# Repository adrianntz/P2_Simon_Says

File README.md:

# P2_Simon_Says
Proiect Simplu proiectat cu microcontroller AVR ATMEGA164A pentru a creea un joc simplu de tip Simon Says, folosind 4 butoane pentru user input si 4 led-uri pentru system output. 

## Inspiratie Proiect
Ideea de functionare a jocului a fost preluata din acest proiect pe arduino:

https://youtu.be/xLLTxN_UBnI

## Firmware Architecture
Bootloader-ul pentru Atmega164A este deja incarcat inainte de primirea chip-ului. Firmware-ul poate fi flashed folosind programul AvrBuster.exe
Firmware-ul pentru Atmega164A este scris in C folosind compilatorul CodeVisionAVR ANSI C Compiler si IDE-ul CodeVisionAVR. Codul in C  a fost creat folosind Code Wizard-ul IDE-ului.
Pentru jocul Simon Says vom folosi doar Portul B al microcontrollerului. Astfel, cu Code Wizard am initializat Pinii PB0->3 ca input si conectati la rezistorul pull-up intern, acesti pini fiind conectati la switch-uri, iar pinii PB4->7 sunt de tip output prin care aprindem LED-urile.
Codul are ca structura principala doi vectori de lungime MAX_LEVEL, unul fiind lista de secvente a nivelului si al doilea fiind secventa introdusa de catre jucator.
Astfel, lungimea jocului poate fi setata folosind MAX_LEVEL. La pornirea firmware-ului se umple vectorul nivelului cu valori randomizate intre 0 si 4. De-a lungul jocului se completeaza si vectorul cu secventele introduse de jucator, si se vor compara ce doi vetori. In momentul in care se greseste o secventa sau se ajunge la lungimea maxima, se termina jocul si se reseteaza vectorii.
De asemenea Firmware-ul are implementat o dificultate a jocului, anume viteza afisarii secventei curente. Cu cat este mai avansat jocul intr-o secventa mai mare, aceasta viteza creste, facand jocul mai dificil cu cat te joci mai mult.

Utilizare Memorie Firmware:
EEPROM usage: 0 byte(s), 0.0% of EEPROM

Program size: 646 words (1292 bytes), 7.9% of FLASH

RAM Global variables size: 404 byte(s)

Estimated Data Stack usage: 6 byte(s)

(Informatie data de compilator)

## Hadware Description
Placuta THT este compusa dintr-un microcontroller ATMEGA164A cu footprint THD si componentele sale auxiliare (condensatoare, quartz si un LED pentru verificare), iar portul A al microcontrollerului este impartit jumate in input si output. Jumatea de input a portului B este conectat la 4 butoane la GND, iar jumatea de output este conectat la 4 led-uri. Alimentarea se face printr-un USB bridge bazat pe chip-ul CH340G USB to Serial Converter.

Varianta SMD introduce un package mai mic pentru toate componentele, ATMEGA164A fiind pe footprint TQFP si toate rezistoarele, condensatoare si led-urile pe footprint 0805. Bridge-ul USB to Serial este incorporat in placuta conectat la un port micro-USB pus pe placuta.
## Hardware Schematic 

## Hardware PCB Layout

## BOM 

| Component Count:               | 39   |                   |                                                            |                                                         |
|--------------------------------|------|-------------------|------------------------------------------------------------|---------------------------------------------------------|
| Ref                            | Qnty | Value             | Footprint                                                  | Description                                             |
| C1, C5,                        | 2    | 18p               | Capacitor_SMD:C_0805_2012Metric                            | Capacitor symbol for simulation only                    |
| C2, C4, C6, C11,               | 4    | 100n              | Capacitor_SMD:C_0805_2012Metric                            | Capacitor symbol for simulation only                    |
| C3,                            | 1    | 1u                | Capacitor_Tantalum_SMD:CP_EIA-3216-18_Kemet-A              | Polarized capacitor                                     |
| C7, C9,                        | 2    | 22p               | Capacitor_SMD:C_0805_2012Metric                            | Capacitor symbol for simulation only                    |
| C8,                            | 1    | 22u               | Capacitor_Tantalum_SMD:CP_EIA-3216-12_Kemet-S              | Capacitor symbol for simulation only                    |
| C10,                           | 1    | 10n               | Capacitor_SMD:C_0805_2012Metric                            | Capacitor symbol for simulation only                    |
| D1,                            | 1    | RED LED           | LED_SMD:LED_0805_2012Metric                                | Light emitting diode                                    |
| D2, D6,                        | 2    | RED  LED          | LED_SMD:LED_0805_2012Metric                                | Light emitting diode                                    |
| D3,                            | 1    | GEEN LED          | LED_SMD:LED_0805_2012Metric                                | Light emitting diode                                    |
| D4,                            | 1    | BLUE LED          | LED_SMD:LED_0805_2012Metric                                | Light emitting diode                                    |
| D5,                            | 1    | ORANGE LED        | LED_SMD:LED_0805_2012Metric                                | Light emitting diode                                    |
| J1, J2, J3, J4,                | 4    | Conn_01x08_Female | Connector_PinHeader_1.00mm:PinHeader_1x08_P1.00mm_Vertical | Generic 1x8 Connector                                   |
| J5,                            | 1    | USB_A             | Connector_USB:USB_A_Molex_67643_Horizontal                 | USB Type A connector                                    |
| R1,                            | 1    | 10k               | Resistor_SMD:R_0805_2012Metric                             | Resistor                                                |
| R2,                            | 1    | 470               | Resistor_SMD:R_0805_2012Metric                             | Resistor                                                |
| R3, R4, R5, R6,                | 4    | 100               | Resistor_SMD:R_0805_2012Metric                             | Resistor                                                |
| R7,                            | 1    | 220               | Resistor_SMD:R_0805_2012Metric                             | Resistor                                                |
| SW1, SW2, SW3, SW4, SW5, SW6,  | 6    | SW_MEC_5G         | Button_Switch_SMD:SW_MEC_5GSH9                             | MEC 5G single pole normally-open tactile switch         |
| U1,                            | 1    | ATmega16A-AU      | Package_QFP:TQFP-44_10x10mm_P0.8mm                         | 16MHz, 16kB Flash, 1kB SRAM, 512B EEPROM, JTAG, TQFP-44 |
| U2,                            | 1    | CH340G            | Package_SO:SOIC-16_3.9x9.9mm_P1.27mm                       | USB serial converter, UART, SOIC-16                     |
| Y1,                            | 1    | 20MHz             | Crystal:Crystal_SMD_HC49-SD_HandSoldering                  | Two pin crystal                                         |
| Y2,                            | 1    | 12MHz             | Crystal:Crystal_SMD_HC49-SD_HandSoldering                  | Two pin crystal                                         |

## Bibliography

https://create.arduino.cc/projecthub/bernieri/genius-game-simon-0e76dc

https://www.youtube.com/watch?v=xLLTxN_UBnI

http://ww1.microchip.com/downloads/en/devicedoc/atmel-8272-8-bit-avr-microcontroller-atmega164a_pa-324a_pa-644a_pa-1284_p_datasheet.pdf

https://cdn.sparkfun.com/datasheets/Dev/Arduino/Other/CH340DS1.PDF

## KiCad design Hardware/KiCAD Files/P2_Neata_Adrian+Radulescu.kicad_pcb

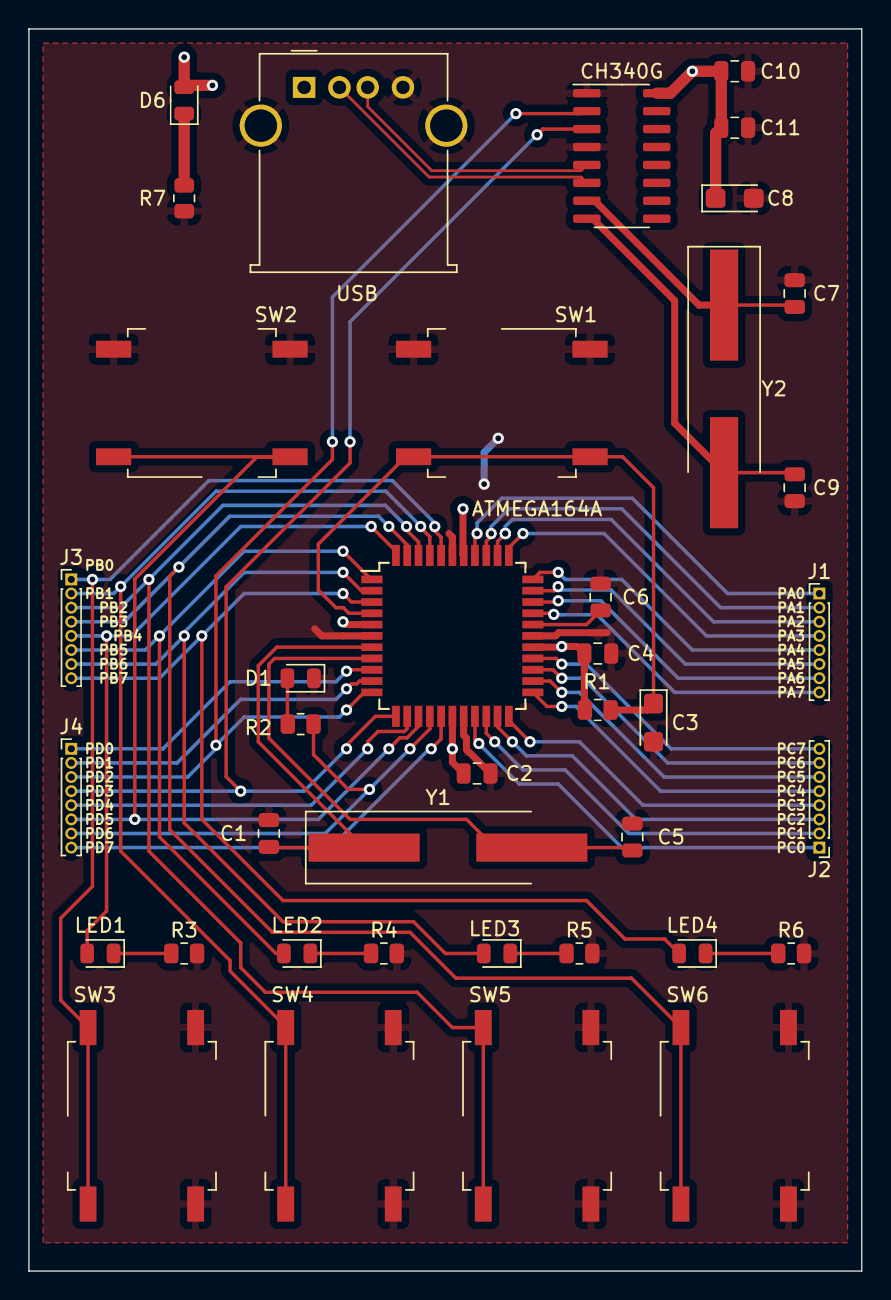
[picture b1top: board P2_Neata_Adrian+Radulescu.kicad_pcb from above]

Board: 2 copper layers, 59.0 x 88.0 mm, 39 parts (0 on the bottom side), 48 nets.

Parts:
ATMEGA164A: ATmega16A-AU; TQFP-44_10x10mm_P0.8mm
C1, C5: 18p; C_0805_2012Metric
C2, C4, C6, C11: 100n; C_0805_2012Metric
C3: 1u; CP_EIA-3216-18_Kemet-A
C7, C9: 22p; C_0805_2012Metric
C8: 22u; CP_EIA-3216-12_Kemet-S
C10: 10n; C_0805_2012Metric
CH340G: CH340G; SOIC-16_3.9x9.9mm_P1.27mm
D1, D6: RED LED; LED_0805_2012Metric
J1, J2, J3, J4: Conn_01x08_Female; PinHeader_1x08_P1.00mm_Vertical
LED1: RED LED; LED_0805_2012Metric
LED2: GEEN LED; LED_0805_2012Metric
LED3: BLUE LED; LED_0805_2012Metric
LED4: ORANGE LED; LED_0805_2012Metric
R1: 10k; R_0805_2012Metric
R2: 470; R_0805_2012Metric
R3, R4, R5, R6: 100; R_0805_2012Metric
R7: 220; R_0805_2012Metric
SW1, SW2, SW3, SW4, SW5, SW6: SW_MEC_5G; SW_MEC_5GSH9
USB: USB_A; USB_A_Molex_67643_Horizontal
Y1: 20MHz; Crystal_SMD_HC49-SD_HandSoldering
Y2: 12MHz; Crystal_SMD_HC49-SD_HandSoldering

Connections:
+5V: ATMEGA164A.5, ATMEGA164A.17, ATMEGA164A.27, ATMEGA164A.38, C2.1, C4.1, C8.1, C10.1, C11.1, CH340G.16, D6.2, R1.2, USB.1
AVR_PB0: ATMEGA164A.40, J3.1, SW3.1, SW3.2
AVR_PB1: ATMEGA164A.41, J3.2, SW4.1, SW4.2
AVR_PB2: ATMEGA164A.42, J3.3, SW5.1, SW5.2
AVR_PB3: ATMEGA164A.43, J3.4, SW6.1, SW6.2
AVR_PB4: ATMEGA164A.44, J3.5, LED1.2
AVR_PB5: ATMEGA164A.1, J3.6, LED2.2
AVR_PB6: ATMEGA164A.2, J3.7, LED3.2
AVR_PB7: ATMEGA164A.3, J3.8, LED4.2
AVR_PD0: ATMEGA164A.9, J4.1
AVR_PD1: ATMEGA164A.10, J4.2
AVR_PD4: ATMEGA164A.13, J4.5
AVR_PD5: ATMEGA164A.14, J4.6, SW2.1, SW2.2
AVR_PD6: ATMEGA164A.15, J4.7, R2.1
AVR_PD7: ATMEGA164A.16, J4.8
AVR_RXD: ATMEGA164A.11, CH340G.2, J4.3
AVR_TXD: ATMEGA164A.12, CH340G.3, J4.4
AVR_XTAL1: ATMEGA164A.8, C5.1, Y1.2
AVR_XTAL2: ATMEGA164A.7, C1.1, Y1.1
GND: ATMEGA164A.6, ATMEGA164A.18, ATMEGA164A.28, ATMEGA164A.39, C1.2, C2.2, C3.2, C4.2, C5.2, C6.2, C7.2, C8.2, C9.2, C10.2, C11.2, CH340G.1, CH340G.4, D1.1, R3.2, R4.2, R5.2, R6.2, R7.2, SW1.1, SW1.2, SW2.3, SW2.4, SW3.3, SW3.4, SW4.3, SW4.4, SW5.3, SW5.4, SW6.3, SW6.4, USB.4, USB.5
unnamed: ATMEGA164A.4, C3.1, R1.1, SW1.3, SW1.4
unnamed: ATMEGA164A.29, C6.1
unnamed: C7.1, CH340G.7, Y2.1
unnamed: C9.1, CH340G.8, Y2.2
unnamed: D1.2, R2.2
unnamed: LED1.1, R3.1
unnamed: LED2.1, R4.1
unnamed: LED3.1, R5.1
unnamed: LED4.1, R6.1
unnamed: D6.1, R7.1
unnamed: ATMEGA164A.37, J1.1
unnamed: ATMEGA164A.36, J1.2
unnamed: ATMEGA164A.35, J1.3
unnamed: ATMEGA164A.34, J1.4
unnamed: ATMEGA164A.33, J1.5
unnamed: ATMEGA164A.32, J1.6
unnamed: ATMEGA164A.31, J1.7
unnamed: ATMEGA164A.30, J1.8
unnamed: ATMEGA164A.19, J2.1
unnamed: ATMEGA164A.20, J2.2
unnamed: ATMEGA164A.21, J2.3
unnamed: ATMEGA164A.22, J2.4
unnamed: ATMEGA164A.23, J2.5
unnamed: ATMEGA164A.24, J2.6
unnamed: ATMEGA164A.25, J2.7
unnamed: ATMEGA164A.26, J2.8
USB_D+: CH340G.5, USB.3
USB_D-: CH340G.6, USB.2

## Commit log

2022-06-15 First Commit: Added initial Firmware, Hardware Schematic and layout and Documentation files to the repository.
2022-06-15 2nd Commit: Added BOM Files for the hardware schematic.
2022-06-15 Updated Readme.md file
2022-06-15 Updated Readme.md again.
2022-06-15 Updated Firmware to add end seqence when the player reaches the maximum level successfully
2022-06-15 Updated Readme.md, adding RAM and Flash used by the firmware and Bibliography
2022-06-15 Updated Readme.md by adding hardware description in both THD and SMD format
2022-06-15 Added PCB lauyout files and updated HTML Documentation
2022-06-15 Updated Readme.md to add layout picture
2022-06-15 Added PCB Layout picture to Hardware files
2022-06-16 Added Updated HTML Documentation with Github Link
2022-06-16 Updated error on Port used. Changed from PORTA->PORTB
